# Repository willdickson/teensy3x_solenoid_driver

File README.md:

# teensy3x_solenoid_driver 
A teensy3x expansion board for driver solenoid valves.

# License: 
Creative Commons Attribution 4.0 International CC BY 4.0

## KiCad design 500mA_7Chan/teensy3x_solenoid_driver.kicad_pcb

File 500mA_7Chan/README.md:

# teensy3x_solenoid_driver 
A teensy3x expansion board for driving solenoid valves.

# License: 
Creative Commons Attribution 4.0 International CC BY 4.0

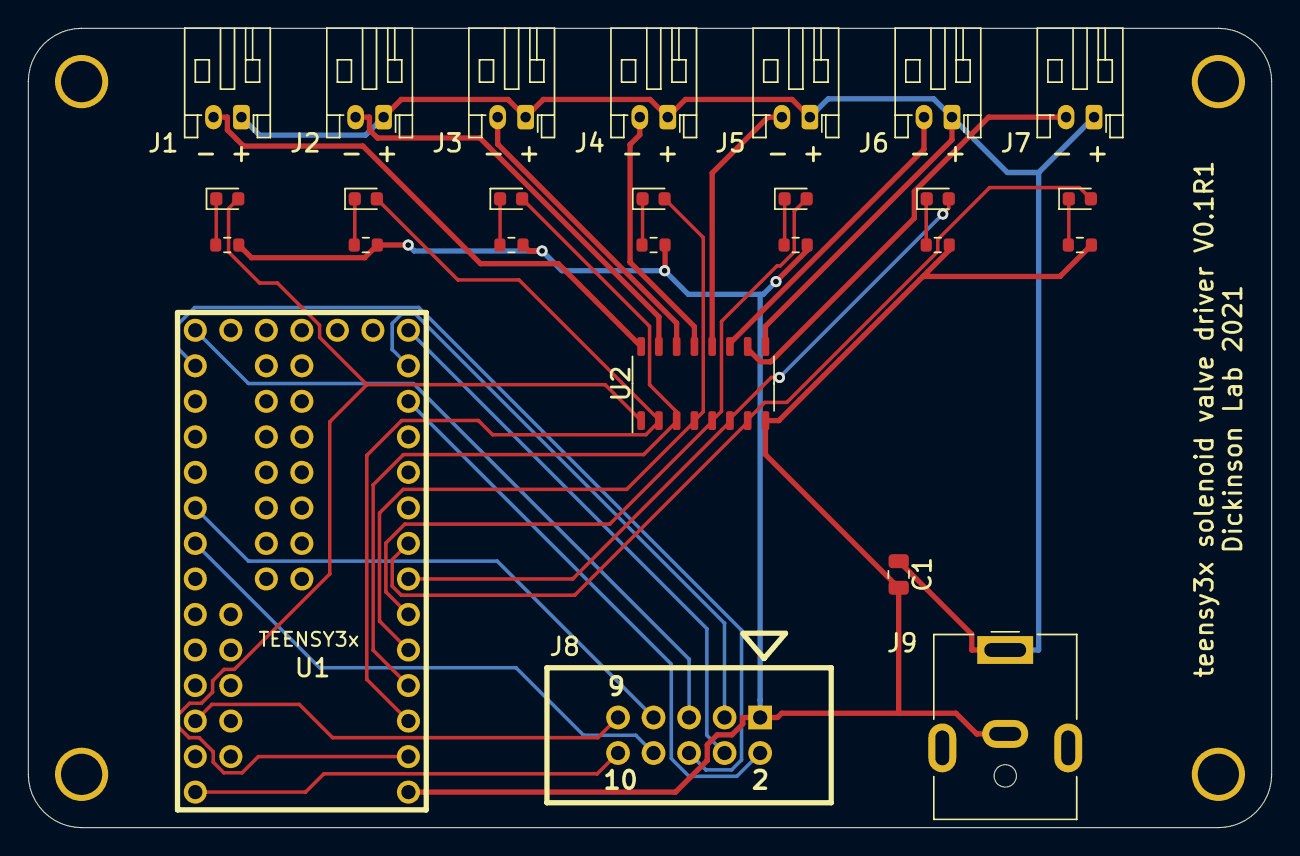
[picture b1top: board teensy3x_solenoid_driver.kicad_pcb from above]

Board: 2 copper layers, 88.9 x 57.2 mm, 30 parts (0 on the bottom side), 32 nets.

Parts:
C1: 10uF; C_0805_2012Metric
D1, D2, D3, D4, D5, D6, D7: LED_ALT; LED_0603_1608Metric
J1, J2, J3, J4, J5, J6, J7: Conn_01x02; JST_PH_S2B-PH-K_1x02_P2.00mm_Horizontal
J8: Conn_02x05_Odd_Even; 5X2_SHRD_HEADER
J9: Jack-DC; BarrelJack_CUI_PJ-063AH_Horizontal
M1, M2, M3, M4: VAL**; 4-40
R1, R2, R3, R4, R5, R6, R7: 330; R_0603_1608Metric
U1: TEENSY3x; TEENSY3X
U2: TBD62003A; SOP-16_3.9x9.9mm_P1.27mm

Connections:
/3V3: J8.9, U1.31
/5V: J8.10, U1.33
/D10_CS: J8.2, U1.12
/D11_MOSI: J8.3, U1.13
/D12_MISO: J8.4, U1.14
/D13_SCK: J8.5, U1.20
/D14_A0: J8.6, U1.21
/D18_SDA0: J8.7, U1.25
/D19_SCL0: J8.8, U1.26
GND: C1.2, J8.1, J9.2, R1.2, R2.2, R3.2, R4.2, R5.2, R6.2, R7.2, U1.1, U2.8
unnamed: C1.1, J1.1, J2.1, J3.1, J4.1, J5.1, J6.1, J7.1, J9.1, U2.9
unnamed: D1.1, R1.1
unnamed: D1.2, U1.2, U2.1
unnamed: D2.1, R2.1
unnamed: D2.2, U1.3, U2.2
unnamed: D3.1, R3.1
unnamed: D3.2, U1.4, U2.3
unnamed: D4.1, R4.1
unnamed: D4.2, U1.5, U2.4
unnamed: D5.1, R5.1
unnamed: D5.2, U1.6, U2.5
unnamed: D6.1, R6.1
unnamed: D6.2, U1.7, U2.6
unnamed: D7.1, R7.1
unnamed: D7.2, U1.8, U2.7
unnamed: J1.2, U2.16
unnamed: J2.2, U2.15
unnamed: J3.2, U2.14
unnamed: J4.2, U2.13
unnamed: J5.2, U2.12
unnamed: J6.2, U2.11
unnamed: J7.2, U2.10

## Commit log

2021-02-23 Project creation.
2021-02-23 Fixed typo.
2021-02-23 Changed base resistor ... forgot about extra voltage drop due to darlington transistor.
2021-02-24 Added new 7 channel 500mA/channel design based on TBD62003A.
2021-02-24 Moved readme.
2021-02-24 Finished initial layout and routing for 500mA design.
2021-02-25 Added finished initial design of 7channel driver.
2021-02-25 Added copy of license file top level directory.
